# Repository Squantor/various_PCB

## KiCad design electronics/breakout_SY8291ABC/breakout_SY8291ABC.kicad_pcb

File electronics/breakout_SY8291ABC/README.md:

# SY8291ABC breakout board
Breakout for the [SY8291ABC](https://datasheet.lcsc.com/szlcsc/1806040920_Silergy-Corp-SY8291ABC_C125896.pdf) step down converter, can also be used as a LM7805 replacement.
## TODO's
Still some things need to be done:
* Review with one night in between
* Produce at [OSHPARK](https://oshpark.com/)
* Assemble
* Test & characterise
* update Readme.md with pictures and BOM
## BOM
* [SY8291ABC](https://lcsc.com/product-detail/DC-DC-Converters_Silergy-Corp-SY8291ABC_C125896.html)

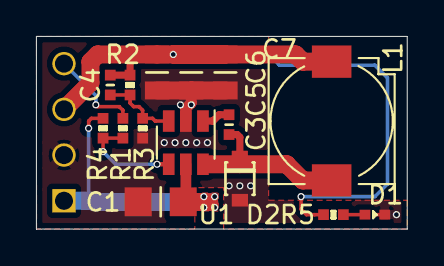
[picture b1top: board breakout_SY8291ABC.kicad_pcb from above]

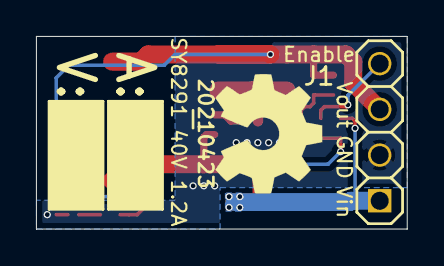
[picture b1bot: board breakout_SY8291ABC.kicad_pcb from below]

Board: 2 copper layers, 20.6 x 10.7 mm, 20 parts (5 on the bottom side), 9 nets.

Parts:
C1: 10u; C_1206_0805
C3: 100n; C_0402
C4: 22p; C_0402
C5, C6, C7: 10u; C_0805
D1: LED; LED_0402_osram
D2: B140WS; SOD_323_onsemi
J1: Conn_01x04; Header-0254-1X04-H010
L1: TBD; L_SLF70XX_TDK_hand
N1: 20210423; Label_Generic
N2: OHWLOGO; OSHW-Symbol_6.7x6mm_SilkScreen
N3: V:; Label_Note_medium
N4: A:; Label_Note_medium
R1: 100; R_0402_hand
R2: 100K; R_0402_hand
R3: TBD; R_0402_hand
R4: 100k; R_0402_hand
R5: 4.7K; R_0402_hand
U1: SY8291; SOT23-6-HAND

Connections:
/Enable: J1.4, R1.2
/FB: C4.2, R2.2, R3.1, U1.3
/GND: C1.2, C5.2, C6.2, C7.2, D1.1, D2.2, J1.2, R3.2, U1.2
/Vin: C1.1, J1.1, R4.2, U1.5
/Vout: C4.1, C5.1, C6.1, C7.1, J1.3, L1.1, R2.1, R5.2
unnamed: C3.1, D2.1, L1.2, U1.6
unnamed: C3.2, U1.1
unnamed: D1.2, R5.1
unnamed: R1.1, R4.1, U1.4

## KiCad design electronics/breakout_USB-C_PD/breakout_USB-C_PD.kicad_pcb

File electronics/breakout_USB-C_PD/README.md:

# USB-C Power delivery breakout board
Simple breakout for USB-C power delivery only pins
## TODO's
Still some things need to be done:
* Review with one night in between
* Produce at [OSHPARK](https://oshpark.com/)
* Assemble
* Test & characterise
* update Readme.md with pictures and BOM
## BOM
* [USB-C PD only connector from LCSC](https://lcsc.com/product-detail/Others_Korean-Hroparts-Elec-TYPE-C-31-M-17_C283540.html)

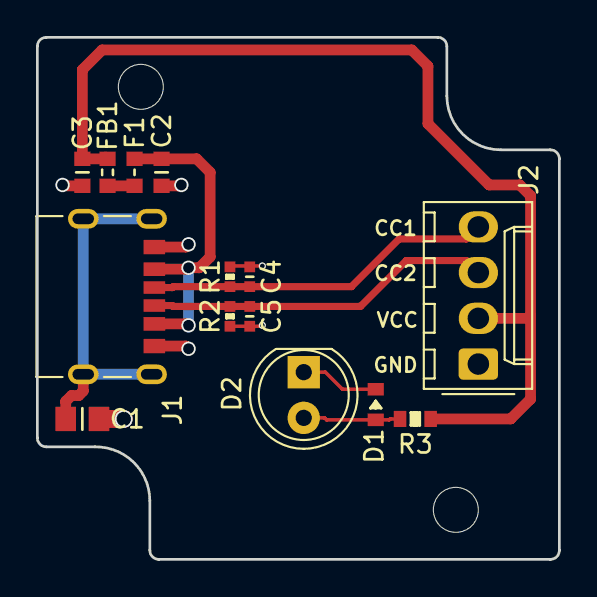
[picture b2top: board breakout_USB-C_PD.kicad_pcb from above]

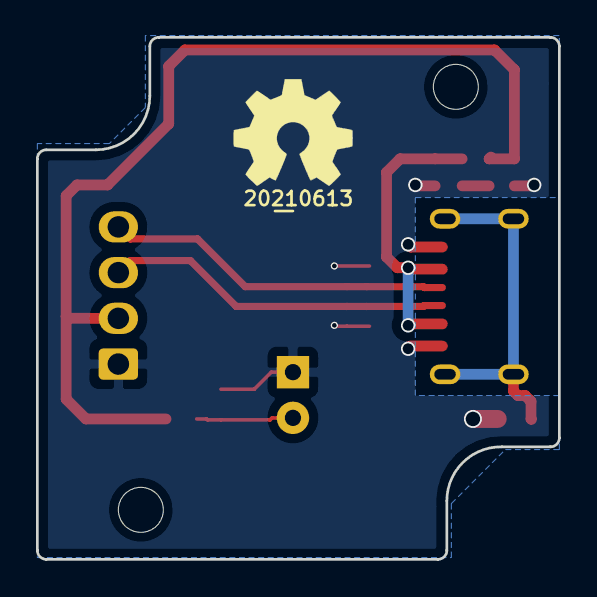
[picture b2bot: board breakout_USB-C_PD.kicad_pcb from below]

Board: 2 copper layers, 29.0 x 29.0 mm, 18 parts (2 on the bottom side), 8 nets.

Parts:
C1: 10n; C_0805+0603
C2: 100n; C_0603
C3: 10u; C_0603
C4, C5: 470p; C_0402
D1: LED; LED_0603_hand
D2: LED; LED_D5.0mm
F1: 500mA; F_0603_hand
FB1: 600; L_0603
H1, H2: Drill_Hole_no_metal; MountingHole_2.5mm_no_metal
J1: USB-C_PD; USB-C-HRO-31-M-17
J2: Conn_01x04; Molex_KK-254_AE-6410-04A_1x04_P2.54mm_Vertical
N1: OHWLOGO; OSHW-Symbol_6.7x6mm_SilkScreen
N2: 20210613; Label_Generic
R1, R2: 5.1K; R_0402_hand
R3: 1K; R_0603_hand

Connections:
/CC1: C4.2, J1.A5, J2.4, R1.2
/CC2: C5.2, J1.B5, J2.3, R2.2
/GND: C1.2, C2.2, C3.2, C4.1, C5.1, D1.1, D2.1, J1.A12, J1.B12, J2.1, R1.1, R2.1
/VBUS: C2.1, F1.2, J1.A9, J1.B9
/VCC: C3.1, FB1.1, J2.2, R3.1
unnamed: C1.1, J1.S
unnamed: D1.2, D2.2, R3.2
unnamed: F1.1, FB1.2

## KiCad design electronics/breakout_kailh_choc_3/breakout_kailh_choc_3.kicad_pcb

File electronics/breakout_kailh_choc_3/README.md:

# 4 button kailh choc breakout
Simple test breakout for the kailh choc buttons
# HSI (Hardware Software Interface)
6 pin connector:
1. LED cathodes row 1
2. LED cathodes row 2
3. Switch Row 1
4. Switch Row 2
5. Column 2
6. Column 1 
## TODO's
Still some things need to be done:
* Review with one night in between
* Produce at [OSHPARK](https://oshpark.com/)
* Assemble
* Test & characterise
* update Readme.md with pictures and BOM
## BOM
* Kailh choc switches
* any SOD523 diode
* Any SMD LED from 1208 to 0603

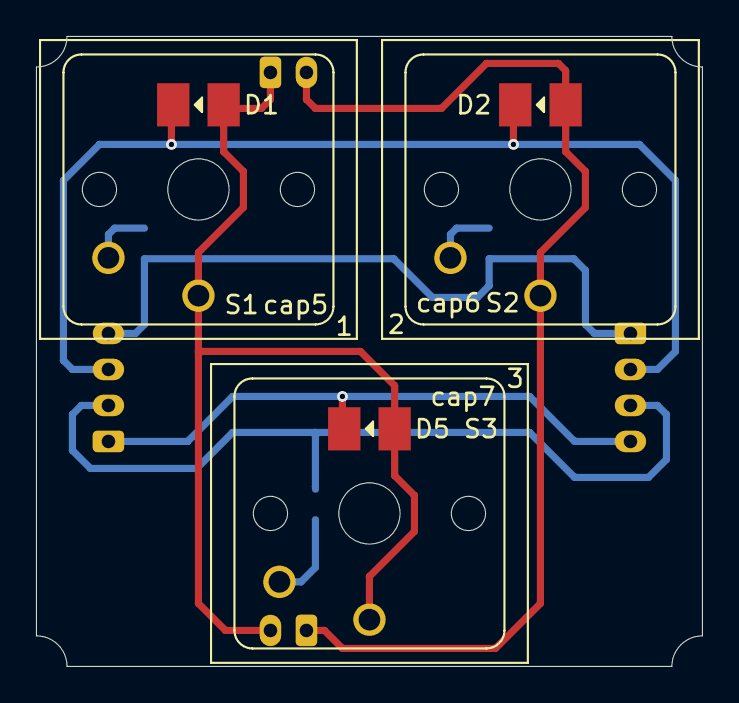
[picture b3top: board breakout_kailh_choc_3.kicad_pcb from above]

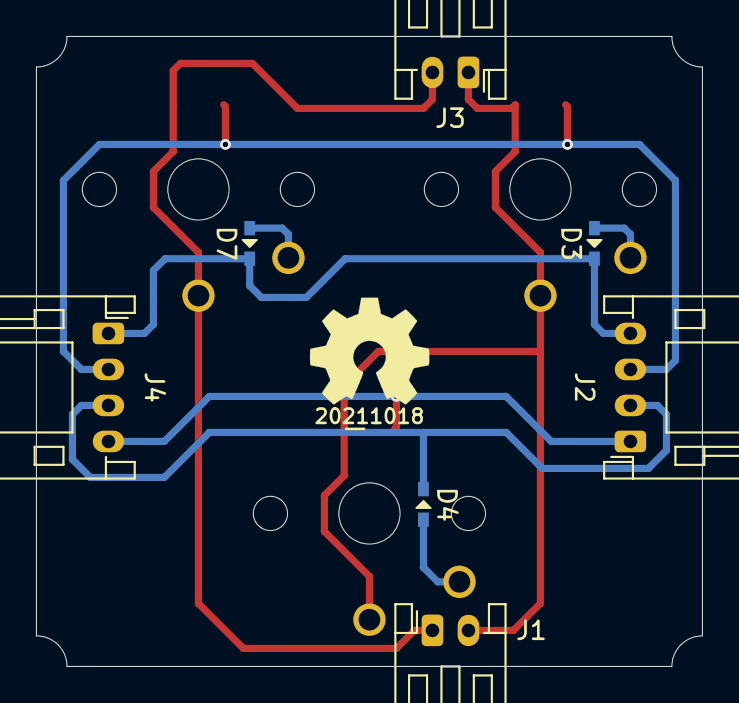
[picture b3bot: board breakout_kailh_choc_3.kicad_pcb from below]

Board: 2 copper layers, 37.0 x 35.0 mm, 18 parts (9 on the bottom side), 9 nets.

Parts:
D1, D2, D5: LED; LED_1208_0603
D3, D4, D7: D; SOD-523_hand
J1, J3: JST_PH; JST_PH_S2B-PH-K_1x02_P2.00mm_Horizontal
J2, J4: JST_PH; JST_PH_S4B-PH-K_1x04_P2.00mm_Horizontal
N1: 20211018; Label_Generic
N2: OHWLOGO; OSHW-Symbol_6.7x6mm_SilkScreen
S1, S2, S3: choc; KAILH_choc_LED
cap5: 1; KAILH_choc_keycap_1
cap6: 2; KAILH_choc_keycap_1
cap7: 3; KAILH_choc_keycap_1

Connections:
/COL1: D1.2, D5.2, J1.2, J3.1, S1.1, S3.1
/COL2: D2.2, J1.1, J3.2, S2.1
/LEDC1: D1.1, D2.1, J2.3, J4.2
/LEDC2: D5.1, J2.1, J4.4
/SWR1: D3.1, D7.1, J2.4, J4.1
/SWR2: D4.1, J2.2, J4.3
unnamed: D3.2, S1.2
unnamed: D4.2, S3.2
unnamed: D7.2, S2.2
